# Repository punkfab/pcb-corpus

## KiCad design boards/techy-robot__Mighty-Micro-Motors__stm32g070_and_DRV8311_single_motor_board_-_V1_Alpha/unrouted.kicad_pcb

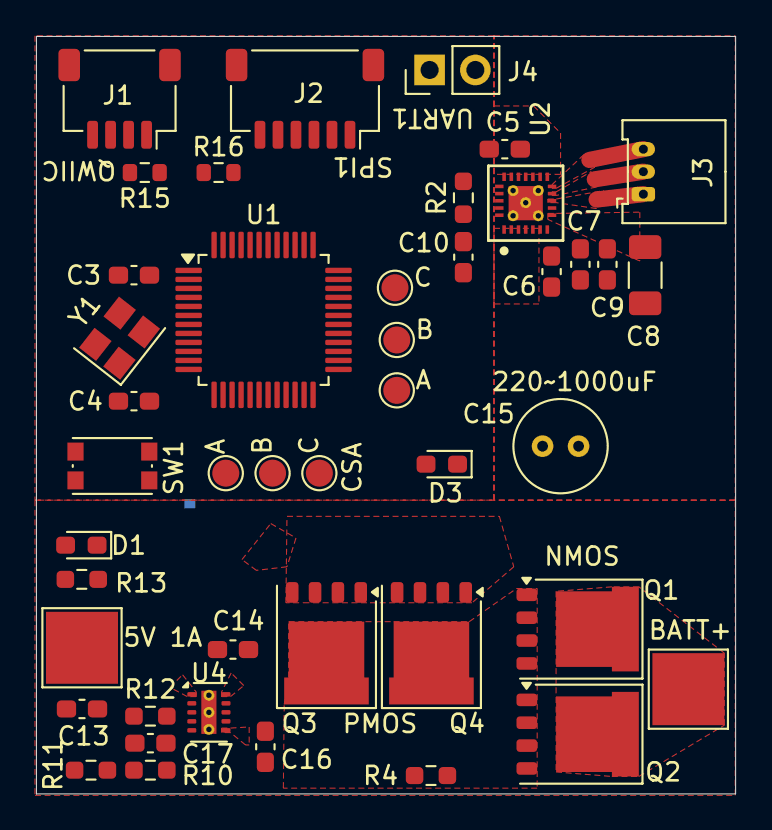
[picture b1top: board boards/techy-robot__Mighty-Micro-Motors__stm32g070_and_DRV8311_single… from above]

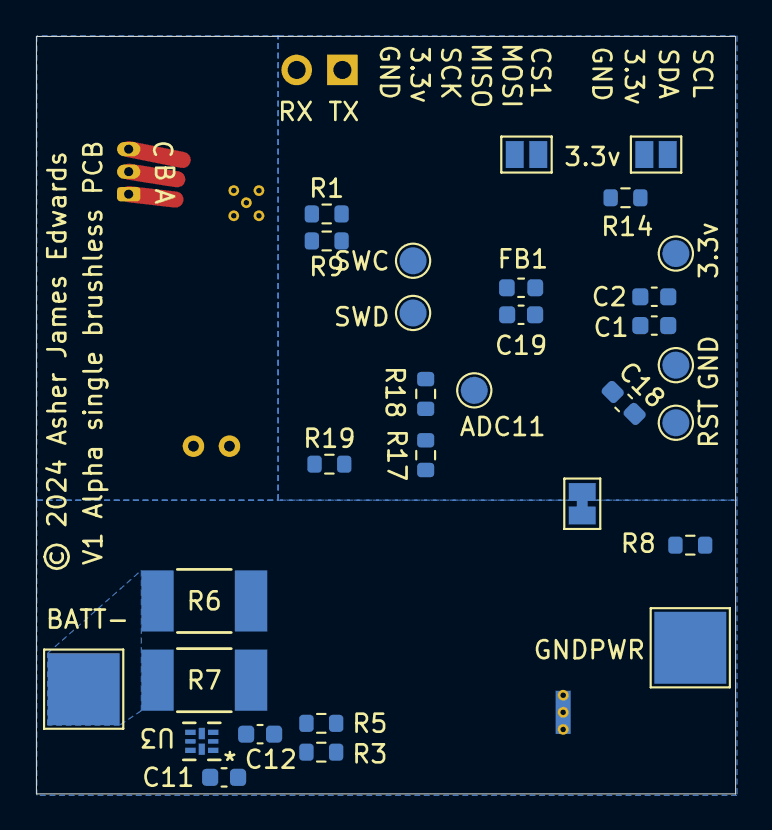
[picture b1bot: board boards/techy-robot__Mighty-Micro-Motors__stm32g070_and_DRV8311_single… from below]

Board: 4 copper layers, 38.8 x 42.1 mm, 74 parts (30 on the bottom side), 51 nets, no tracks yet.

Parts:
C1, C19: 0.1uF; C_0603_1608Metric
C2: 4.7uF; C_0603_1608Metric
C3, C4: 12pF; C_0603_1608Metric_Pad1.08x0.95mm_HandSolder
C5: 4.7uF; C_0603_1608Metric_Pad1.08x0.95mm_HandSolder
C6, C7, C9: 0.1uF, 16v; C_0603_1608Metric_Pad1.08x0.95mm_HandSolder
C8: 220uF, 16 v; C_1206_3216Metric_Pad1.33x1.80mm_HandSolder
C10, C18: 0.1uF; C_0603_1608Metric_Pad1.08x0.95mm_HandSolder
C11: 8nF; C_0603_1608Metric
C12: 1uF, 16v; C_0603_1608Metric
C13, C14, C16: 10uF, 16v; C_0603_1608Metric_Pad1.08x0.95mm_HandSolder
C15: 1000uF, 16v; C_Radial_D5.0mm_H5.0mm_P2.00mm
C17: 1uF; C_0603_1608Metric_Pad1.08x0.95mm_HandSolder
D1, D3: Osram LT Q99G.01 green led; LED_0603_1608Metric_Pad1.05x0.95mm_HandSolder
FB1: 120ohm imp @100mhz; L_0603_1608Metric
H1, H2, H3, H4: 4mm_Pad; TestPoint_Pad_4.0x4.0mm
J1: JST SH SM04B; JST_SH_SM04B-SRSS-TB_1x04-1MP_P1.00mm_Horizontal
J2: JST SH SM06B; JST_SH_SM06B-SRSS-TB_1x06-1MP_P1.00mm_Horizontal
J3: Molex_PicoBlade_53048-0310 Horizontal 3P; Molex_PicoBlade_53048-0310_1x03_P1.25mm_Horizontal
J4: Conn_01x02_Pin; PinHeader_1x02_P2.54mm_Vertical
JP1, JP2: VCC; SolderJumper-2_P1.3mm_Bridged_Pad1.0x1.5mm
L1: GND joiner; SolderJumper-2_P1.3mm_Bridged_Pad1.0x1.5mm
Q1: NMOS, sir404dp; PQFN-8-EP_6x5mm_P1.27mm_Generic
Q2: NMOS; PQFN-8-EP_6x5mm_P1.27mm_Generic
Q3: PMOS,Si7157DP; PQFN-8-EP_6x5mm_P1.27mm_Generic
Q4: PMOS; PQFN-8-EP_6x5mm_P1.27mm_Generic
R1, R17: 100k; R_0603_1608Metric
R2: 47k; R_0603_1608Metric_Pad0.98x0.95mm_HandSolder
R3: 20ohm; R_0603_1608Metric
R4, R13: 2k; R_0603_1608Metric_Pad0.98x0.95mm_HandSolder
R5: 300ohm; R_0603_1608Metric
R6: Same, 1000uOhm; RES_WSLF2512_VIS-M
R7: Vishay WSLF2512, 1%, 300uOhm; RES_WSLF2512_VIS-M
R8: 402 ohm; R_0603_1608Metric
R9, R18: 150k; R_0603_1608Metric
R10, R12: 1k; R_0603_1608Metric_Pad0.98x0.95mm_HandSolder
R11: 230ohm; R_0603_1608Metric_Pad0.98x0.95mm_HandSolder
R14, R15, R16: 10k; R_0603_1608Metric
R19: 80.6 ohm; R_0603_1608Metric
SW1: SW_Push; SW_Push_1P1T_NO_CK_KMR2
TP1, TP2, TP3, TP4, TP5, TP6: TestPoint; TestPoint_Pad_D1.5mm
TP7, TP8, TP9, TP10, TP11, TP12: TestPoint_Pad_D1.5mm
U1: STM32G070CBTr; LQFP-48_7x7mm_P0.5mm
U2: DRV8311HRRWR; DRV8311_0.3mmVias
U3: BQ298012RUGT; RUG8_TEX
U4: BQ25060; WSON-10-1EP_2x3mm_P0.5mm_EP0.84x2.4mm_ThermalVias_0.3mm
Y1: ABM8-16.000MHZ-10-1-U-T; Crystal_SMD_Abracon_ABM8G-4Pin_3.2x2.5mm

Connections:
/1A: TP7.1, U1.20 (PB1), U1.26 (PB14), U1.27 (PB15), U2.15 (INHA)
/1B: TP8.1, U1.28 (PA8), U1.29 (PA9/NC), U1.30 (PC6), U2.14 (INHB)
/1C: TP9.1, U1.31 (PC7), U1.32 (PA10/NC), U1.33 (PA11/PA9), U2.13 (INHC)
/1CSA-A: TP10.1, U1.11 (PA0), U1.12 (PA1), U1.13 (PA2), U2.5 (SOA)
/1CSA-B: TP11.1, U1.14 (PA3), U1.15 (PA4), U1.16 (PA5), U2.4 (SOB)
/1CSA-C: TP12.1, U1.17 (PA6), U1.18 (PA7), U1.19 (PB0), U2.3 (SOC)
/ADC10/VBATT: R17.1, R18.2, U1.21 (PB2)
/ADC11: TP6.1, U1.22 (PB10)
/CS1: J2.6, R16.2, U1.40 (PD2)
/LED: R19.1, U1.24 (PB12)
/MISO1: J2.4, U1.43 (PB4)
/MOSI1: J2.5, U1.44 (PB5)
/MOTORPWR: C6.2, C7.1, C8.1, C9.1, C14.1, C15.1, Q3.1 (S), Q3.2 (S), Q3.3 (S), Q4.1 (S), Q4.2 (S), Q4.3 (S), R1.2, R17.2, U2.7 (VIN_AVDD), U2.8 (VM), U4.10 (OUT)
/NRST: C18.1, SW1.2, TP1.1, U1.10 (NRST)
/PSU/BATT+: H1.1, Q1.5 (D), Q2.5 (D), R3.1, R5.1
/PSU/BATT-: C12.2, H2.1, R6.1, R7.1, U3.3 (VSS), U3.5 (CTR)
/PSU/IN: C13.1, H3.1, U4.1 (IN)
/PSU/LDO 4.9v: C17.2, R8.1, R10.1, R13.2, U4.4 (LDO)
/PSU/Pack+: C16.2, Q1.1 (S), Q1.2 (S), Q1.3 (S), Q2.1 (S), Q2.2 (S), Q2.3 (S), Q3.5 (D), Q4.5 (D), R4.1, U4.6 (BAT)
/PSU/~CHG: D1.1 (K), R13.1, U4.8 (~CHG)
/SCK1: J2.3, U1.42 (PB3)
/SCL1: J1.4, R15.2, U1.47 (PB8)
/SDA1: J1.3, R14.2, U1.48 (PB9)
/SWC: TP3.1, U1.36 (PA14)
/SWD: TP2.1, U1.35 (PA13)
/USART1_RX: J4.2, U1.46 (PB7)
/USART1_TX: J4.1, U1.45 (PB6)
GND: C1.2, C2.2, C3.2, C4.2, C5.1, C7.2, C10.1, C17.1, C18.2, C19.1, D3.1 (K), J1.1, J1.MP (MountPin), J2.1, J2.MP (MountPin), L1.1, R2.1, R9.1, R11.2, R12.1, R18.1, SW1.1, TP5.1, U1.7 (VSS), U2.16 (AGND), U4.7 (EN), Y1.2, Y1.4
GNDPWR: C8.2, C9.2, C11.2, C13.2, C14.2, C15.2, C16.1, H4.1, L1.2, R6.2, R7.2, U2.9 (PGND), U2.25 (PowerPAD), U3.4 (CS), U4.3 (VSS), U4.11 (VSS)
unnamed: D1.2 (A), R8.2
unnamed: D3.2 (A), R19.2
unnamed: J1.2, JP1.2 (B)
unnamed: J2.2, JP2.2 (B)
unnamed: J3.1, U2.10 (OUTA)
unnamed: J3.2, U2.11 (OUTB)
unnamed: J3.3, U2.12 (OUTC)
unnamed: Q1.4 (G), Q2.4 (G), U3.7 (DSG)
unnamed: Q3.4 (G), Q4.4 (G), U4.9 (BGATE)
unnamed: C3.1, U1.8 (PF0), Y1.3
unnamed: C4.1, U1.9 (PF1), Y1.1
unnamed: C19.2, FB1.1, U1.5 (VREF+)
unnamed: C6.1, U2.6 (CP)
unnamed: R2.2, U2.21 (GAIN)
unnamed: R1.1, R9.2, U2.24 (SLEEP_N)
unnamed: R3.2, U3.1 (BAT)
unnamed: C11.1, U3.8 (CHG)
unnamed: R4.2, U3.6 (PACK)
unnamed: C12.1, R5.2, U3.2 (VDD)
unnamed: R12.2, U4.2 (ISET)
unnamed: R10.2, R11.1, U4.5 (TS)
VDD: C1.1, C2.1, C5.2, C10.2, FB1.2, JP1.1 (A), JP2.1 (A), R14.1, R15.1, R16.1, TP4.1, U1.4 (VBAT), U1.6 (VDD), U2.2 (CSAREF), U2.17 (AVDD), U2.18 (INLA), U2.19 (INLB), U2.20 (INLC), U2.23 (MODE)

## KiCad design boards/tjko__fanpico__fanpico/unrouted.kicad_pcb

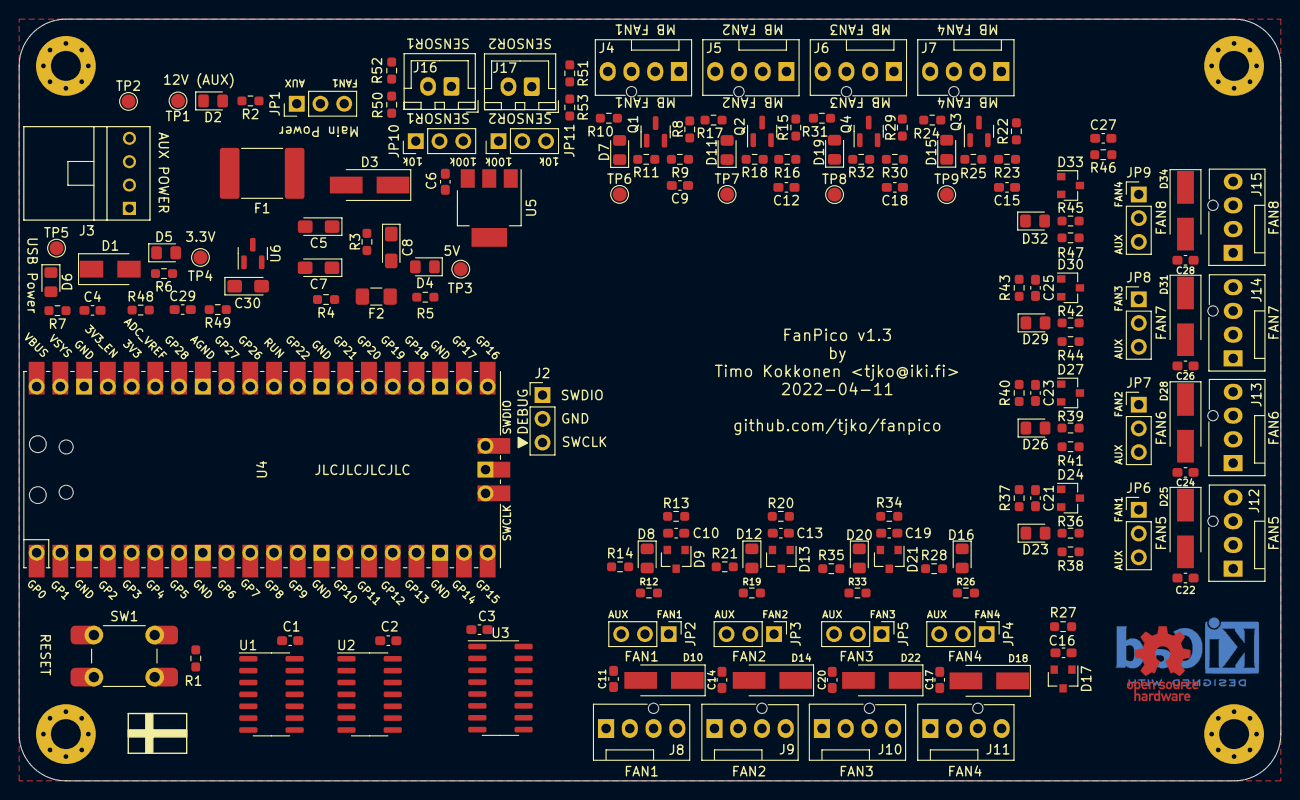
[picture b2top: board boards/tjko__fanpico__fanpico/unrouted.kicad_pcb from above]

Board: 2 copper layers, 135.0 x 81.5 mm, 170 parts (0 on the bottom side), 116 nets, no tracks yet.

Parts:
C1, C2, C3, C4, C6, C11, C14, C17, C20, C22, C24, C26, C28, C29: 0.1uF; C_0603_1608Metric_Pad1.08x0.95mm_HandSolder
C5: 10uF 20V; CP_EIA-3216-18_Kemet-A_Pad1.58x1.35mm_HandSolder
C7, C8, C30: 10uF 16V; CP_EIA-3216-18_Kemet-A_Pad1.58x1.35mm_HandSolder
C9, C12, C15, C18: DNF; C_0603_1608Metric_Pad1.08x0.95mm_HandSolder
C10, C13, C16, C19, C21, C23, C25, C27: 1nF; C_0603_1608Metric_Pad1.08x0.95mm_HandSolder
D1: SM5819PL 1A 40V; D_SMA
D2, D4, D5, D6, D7, D8, D11, D12, D15, D16, D19, D20, D23, D26, D29, D32: LED 0805 (green); LED_0805_2012Metric_Pad1.15x1.40mm_HandSolder
D3, D10, D14, D18, D22, D25, D28, D31, D34: ES1D 1A 200V; D_SMA_Handsoldering
D9, D13, D17, D21, D24, D27, D30, D33: BAT54C; D_SOT-23_ANK
F1: Polyfuse 3A; Fuse_2920_7451Metric_Pad2.10x5.45mm_HandSolder
F2: Polyfuse 0.5A; Fuse_1206_3216Metric_Pad1.42x1.75mm_HandSolder
H1, H2, H3, H4: MountingHole_Pad; MountingHole_3.2mm_M3_Pad_Via
J2: Pico Debug; PinHeader_1x03_P2.54mm_Vertical
J3: Floppy Power Connector; TE 171826-4 Floppy 4-pin
J4: MB Fan1 Input; FanPinHeader_1x04_P2.54mm_Vertical
J5: MB Fan2 Input; FanPinHeader_1x04_P2.54mm_Vertical
J6: MB Fan3 Input; FanPinHeader_1x04_P2.54mm_Vertical
J7: MB Fan4 Input; FanPinHeader_1x04_P2.54mm_Vertical
J8: Fan1 Output; FanPinHeader_1x04_P2.54mm_Vertical
J9: Fan2 Output; FanPinHeader_1x04_P2.54mm_Vertical
J10: Fan3 Output; FanPinHeader_1x04_P2.54mm_Vertical
J11: Fan4 Output; FanPinHeader_1x04_P2.54mm_Vertical
J12: Fan5 Output; FanPinHeader_1x04_P2.54mm_Vertical
J13: Fan6 Output; FanPinHeader_1x04_P2.54mm_Vertical
J14: Fan7 Output; FanPinHeader_1x04_P2.54mm_Vertical
J15: Fan8 Output; FanPinHeader_1x04_P2.54mm_Vertical
J16: Sensor1; JST_XH_B2B-XH-A_1x02_P2.50mm_Vertical
J17: Sensor2; JST_XH_B2B-XH-A_1x02_P2.50mm_Vertical
JP1: Power Selector; PinHeader_1x03_P2.54mm_Vertical
JP2, JP3, JP4, JP5, JP6, JP7, JP8, JP9: Fan Power; PinHeader_1x03_P2.54mm_Vertical
JP10, JP11: NTC Value; PinHeader_1x03_P2.54mm_Vertical
Q1, Q2, Q3, Q4: 2N7002K; SOT-23
R1, R4, R8, R11, R15, R18, R22, R25, R29, R32: 1k; R_0603_1608Metric_Pad0.98x0.95mm_HandSolder
R2, R10, R12, R17, R19, R24, R26, R31, R33, R36, R39, R42, R45: 49.9k; R_0603_1608Metric_Pad0.98x0.95mm_HandSolder
R3, R48: 330; R_0603_1608Metric_Pad0.98x0.95mm_HandSolder
R5, R7, R13, R20, R27, R34, R37, R40, R43, R46, R50, R51: 10k; R_0603_1608Metric_Pad0.98x0.95mm_HandSolder
R6: 4.99k; R_0603_1608Metric_Pad0.98x0.95mm_HandSolder
R9, R16, R23, R30: 30k; R_0603_1608Metric_Pad0.98x0.95mm_HandSolder
R14, R21, R28, R35, R38, R41, R44, R47: 680; R_0603_1608Metric_Pad0.98x0.95mm_HandSolder
R49: 0; R_0603_1608Metric_Pad0.98x0.95mm_HandSolder
R52, R53: 100k; R_0603_1608Metric_Pad0.98x0.95mm_HandSolder
SW1: SW_Push; SW_PUSH_6mm_SMD_2
TP1, TP2, TP3, TP4, TP5, TP6, TP7, TP8, TP9: TestPoint; TestPoint_Pad_D1.5mm
U1, U2: SN74AHCT125QDRQ1; SOIC-14_3.9x8.7mm_P1.27mm
U3: CD74HC4050NSR; SOIC-16_3.9x9.9mm_P1.27mm
U4: Pico; RPi_Pico_SMD_TH
U5: SPX1117-ADJ; SOT-223
U6: LM4040DBZ-3; SOT-23

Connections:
3V3: C3.1, R6.1, R9.2, R13.2, R16.2, R20.2, R23.2, R27.2, R30.2, R34.2, R37.2, R40.2, R43.2, R46.2, R48.1, TP4.1, U3.1 (VCC), U4.36 (3V3)
+5V: C1.1, C2.1, D1.2 (A), F2.2, R5.1, TP3.1, U1.14 (VCC), U2.14 (VCC)
/Fan Channels/Fan1/PWM_IN: J4.4, R8.2
/Fan Channels/Fan1/PWM_OUT: J8.4, R14.2
/Fan Channels/Fan1/PWR_OUT: C11.1, D10.1 (K), J8.2, JP2.2 (C), R12.1
/Fan Channels/Fan1/TACHO_IN: D9.1 (K), J8.3
/Fan Channels/Fan1/TACHO_OUT: J4.3, Q1.3 (D)
/Fan Channels/Fan2/PWM_IN: J5.4, R15.2
/Fan Channels/Fan2/PWM_OUT: J9.4, R21.2
/Fan Channels/Fan2/PWR_OUT: C14.1, D14.1 (K), J9.2, JP3.2 (C), R19.1
/Fan Channels/Fan2/TACHO_IN: D13.1 (K), J9.3
/Fan Channels/Fan2/TACHO_OUT: J5.3, Q2.3 (D)
/Fan Channels/Fan3/PWM_IN: J6.4, R29.2
/Fan Channels/Fan3/PWM_OUT: J10.4, R35.2
/Fan Channels/Fan3/PWR_OUT: C20.1, D22.1 (K), J10.2, JP5.2 (C), R33.1
/Fan Channels/Fan3/TACHO_IN: D21.1 (K), J10.3
/Fan Channels/Fan3/TACHO_OUT: J6.3, Q4.3 (D)
/Fan Channels/Fan4/PWM_IN: J7.4, R22.2
/Fan Channels/Fan4/PWM_OUT: J11.4, R28.2
/Fan Channels/Fan4/PWR_OUT: C17.1, D18.1 (K), J11.2, JP4.2 (C), R26.1
/Fan Channels/Fan4/TACHO_IN: D17.1 (K), J11.3
/Fan Channels/Fan4/TACHO_OUT: J7.3, Q3.3 (D)
/Fan Channels/Fan5/PWM_OUT: J12.4, R38.2
/Fan Channels/Fan5/PWR_OUT: C22.1, D25.1 (K), J12.2, JP6.2 (C), R36.1
/Fan Channels/Fan5/TACHO_IN: D24.1 (K), J12.3
/Fan Channels/Fan6/PWM_OUT: J13.4, R41.2
/Fan Channels/Fan6/PWR_OUT: C24.1, D28.1 (K), J13.2, JP7.2 (C), R39.1
/Fan Channels/Fan6/TACHO_IN: D27.1 (K), J13.3
/Fan Channels/Fan7/PWM_OUT: J14.4, R44.2
/Fan Channels/Fan7/PWR_OUT: C26.1, D31.1 (K), J14.2, JP8.2 (C), R42.1
/Fan Channels/Fan7/TACHO_IN: D30.1 (K), J14.3
/Fan Channels/Fan8/PWM_OUT: J15.4, R47.2
/Fan Channels/Fan8/PWR_OUT: C28.1, D34.1 (K), J15.2, JP9.2 (C), R45.1
/Fan Channels/Fan8/TACHO_IN: D33.1 (K), J15.3
/PWM0B: U3.6 (3Y), U4.22 (GPIO17)
/PWM1B: U3.10 (4Y), U4.25 (GPIO19)
/PWM2A: U1.2 (1A), U4.6 (GPIO4)
/PWM2B: U1.5 (2A), U4.7 (GPIO5)
/PWM3A: U1.9 (3A), U4.9 (GPIO6)
/PWM3B: U1.12 (4A), U4.10 (GPIO7)
/PWM4A: U2.2 (1A), U4.11 (GPIO8)
/PWM4B: U2.5 (2A), U4.12 (GPIO9)
/PWM5A: U2.9 (3A), U4.14 (GPIO10)
/PWM5B: U2.12 (4A), U4.15 (GPIO11)
/PWM6B: U3.2 (1Y), U4.17 (GPIO13)
/PWM7B: U3.4 (2Y), U4.20 (GPIO15)
/SWCLK: J2.3, U4.41 (SWCLK)
/SWDIO: J2.1, U4.43 (SWDIO)
ADC_REF: C29.1, C30.1, JP10.2 (C), JP11.2 (C), R48.2, U4.35 (ADC_VREF), U6.1 (K)
AGND: C29.2, C30.2, J16.1, J17.1, R49.1, U4.33 (AGND), U6.2 (A)
AUX5V: J3.1, TP2.1
AUX12V: F1.2, JP1.1 (A), JP2.3 (B), JP3.3 (B), JP4.3 (B), JP5.3 (B), JP6.3 (B), JP7.3 (B), JP8.3 (B), JP9.3 (B), R2.1, TP1.1
FAN1_PWM_GEN: R14.1, U1.3 (1Y)
FAN1_PWR: J4.2, JP1.3 (B), JP2.1 (A), JP6.1 (A), R10.1, TP6.1
FAN1_TACHO_READ: C10.1, D9.2 (A), R13.1, U4.4 (GPIO2)
FAN2_PWM_GEN: R21.1, U1.6 (2Y)
FAN2_PWR: J5.2, JP3.1 (A), JP7.1 (A), R17.1, TP7.1
FAN2_TACHO_READ: C13.1, D13.2 (A), R20.1, U4.5 (GPIO3)
FAN3_PWM_GEN: R35.1, U1.8 (3Y)
FAN3_PWR: J6.2, JP5.1 (A), JP8.1 (A), R31.1, TP8.1
FAN3_TACHO_READ: C19.1, D21.2 (A), R34.1, U4.26 (GPIO20)
FAN4_PWM_GEN: R28.1, U1.11 (4Y)
FAN4_PWR: J7.2, JP4.1 (A), JP9.1 (A), R24.1, TP9.1
FAN4_TACHO_READ: C16.1, D17.2 (A), R27.1, U4.27 (GPIO21)
FAN5_PWM_GEN: R38.1, U2.3 (1Y)
FAN5_TACHO_READ: C21.1, D24.2 (A), R37.1, U4.29 (GPIO22)
FAN6_PWM_GEN: R41.1, U2.6 (2Y)
FAN6_TACHO_READ: C23.1, D27.2 (A), R40.1, U4.31 (GPIO26_ADC0)
FAN7_PWM_GEN: R44.1, U2.8 (3Y)
FAN7_TACHO_READ: C25.1, D30.2 (A), R43.1, U4.2 (GPIO1)
FAN8_PWM_GEN: R47.1, U2.11 (4Y)
FAN8_TACHO_READ: C27.1, D33.2 (A), R46.1, U4.1 (GPIO0)
GND: C1.2, C2.2, C3.2, C4.2, C5.2, C6.2, C7.2, C8.2, C9.2, C10.2, C11.2, C12.2, C13.2, C14.2, C15.2, C16.2, C17.2, C18.2, C19.2, C20.2, C21.2, C22.2, C23.2, C24.2, C25.2, C26.2, C27.2, C28.2, D2.1 (K), D4.1 (K), D5.1 (K), D6.1 (K), D7.1 (K), D8.1 (K), D10.2 (A), D11.1 (K), D12.1 (K), D14.2 (A), D15.1 (K), D16.1 (K), D18.2 (A), D19.1 (K), D20.1 (K), D22.2 (A), D23.1 (K), D25.2 (A), D26.1 (K), D28.2 (A), D29.1 (K), D31.2 (A), D32.1 (K), D34.2 (A), H1.1, H2.1, H3.1, H4.1, J2.2, J3.2, J3.3, J4.1, J5.1, J6.1, J7.1, J8.1, J9.1, J10.1, J11.1, J12.1, J13.1, J14.1, J15.1, Q1.2 (S), Q2.2 (S), Q3.2 (S), Q4.2 (S), R4.2, R49.2, SW1.2, U1.1 (~1OE), U1.4 (~2OE), U1.7 (GND), U1.10 (~3OE), U1.13 (~4OE), U2.1 (~1OE), U2.4 (~2OE), U2.7 (GND), U2.10 (~3OE), U2.13 (~4OE), U3.8 (GND), U3.11 (5A), U3.14 (6A), U4.3 (GND), U4.8 (GND), U4.13 (GND), U4.18 (GND), U4.23 (GND), U4.28 (GND), U4.38 (GND), U4.42 (GND)
MBFAN1_PWM_READ: C9.1, R8.1, R9.1, U3.3 (1A)
MBFAN1_TACHO_GEN: R11.2, U4.16 (GPIO12)
MBFAN2_PWM_READ: C12.1, R15.1, R16.1, U3.5 (2A)
MBFAN2_TACHO_GEN: R18.2, U4.19 (GPIO14)
MBFAN3_PWM_READ: C18.1, R29.1, R30.1, U3.7 (3A)
MBFAN3_TACHO_GEN: R32.2, U4.21 (GPIO16)
MBFAN4_PWM_READ: C15.1, R22.1, R23.1, U3.9 (4A)
MBFAN4_TACHO_GEN: R25.2, U4.24 (GPIO18)
unnamed: C4.1, D1.1 (K), U4.39 (VSYS)
unnamed: C5.1, C6.1, D3.1 (K), U5.3 (VI)
unnamed: C7.1, R3.2, R4.1, U5.1 (ADJ)
unnamed: C8.1, F2.1, R3.1, U5.2 (VO)
unnamed: D2.2 (A), R2.2
unnamed: D3.2 (A), JP1.2 (C)
unnamed: D4.2 (A), R5.2
unnamed: D5.2 (A), R6.2
unnamed: D6.2 (A), R7.2
unnamed: D7.2 (A), R10.2
unnamed: D8.2 (A), R12.2
unnamed: D11.2 (A), R17.2
unnamed: D12.2 (A), R19.2
unnamed: D15.2 (A), R24.2
unnamed: D16.2 (A), R26.2
unnamed: D19.2 (A), R31.2
unnamed: D20.2 (A), R33.2
unnamed: D23.2 (A), R36.2
unnamed: D26.2 (A), R39.2
unnamed: D29.2 (A), R42.2
unnamed: D32.2 (A), R45.2
unnamed: F1.1, J3.4
unnamed: JP10.1 (A), R50.2
unnamed: JP10.3 (B), R52.2
unnamed: JP11.1 (A), R51.2
unnamed: JP11.3 (B), R53.2
unnamed: Q1.1 (G), R11.1
unnamed: Q2.1 (G), R18.1
unnamed: Q3.1 (G), R25.1
unnamed: Q4.1 (G), R32.1
unnamed: R1.2, SW1.1
RESET: R1.1, U4.30 (RUN)
TEMP1_READ: J16.2, R50.1, R52.1, U4.32 (GPIO27_ADC1)
TEMP2_READ: J17.2, R51.1, R53.1, U4.34 (GPIO28_ADC2)
VBUS: R7.1, TP5.1, U4.40 (VBUS)

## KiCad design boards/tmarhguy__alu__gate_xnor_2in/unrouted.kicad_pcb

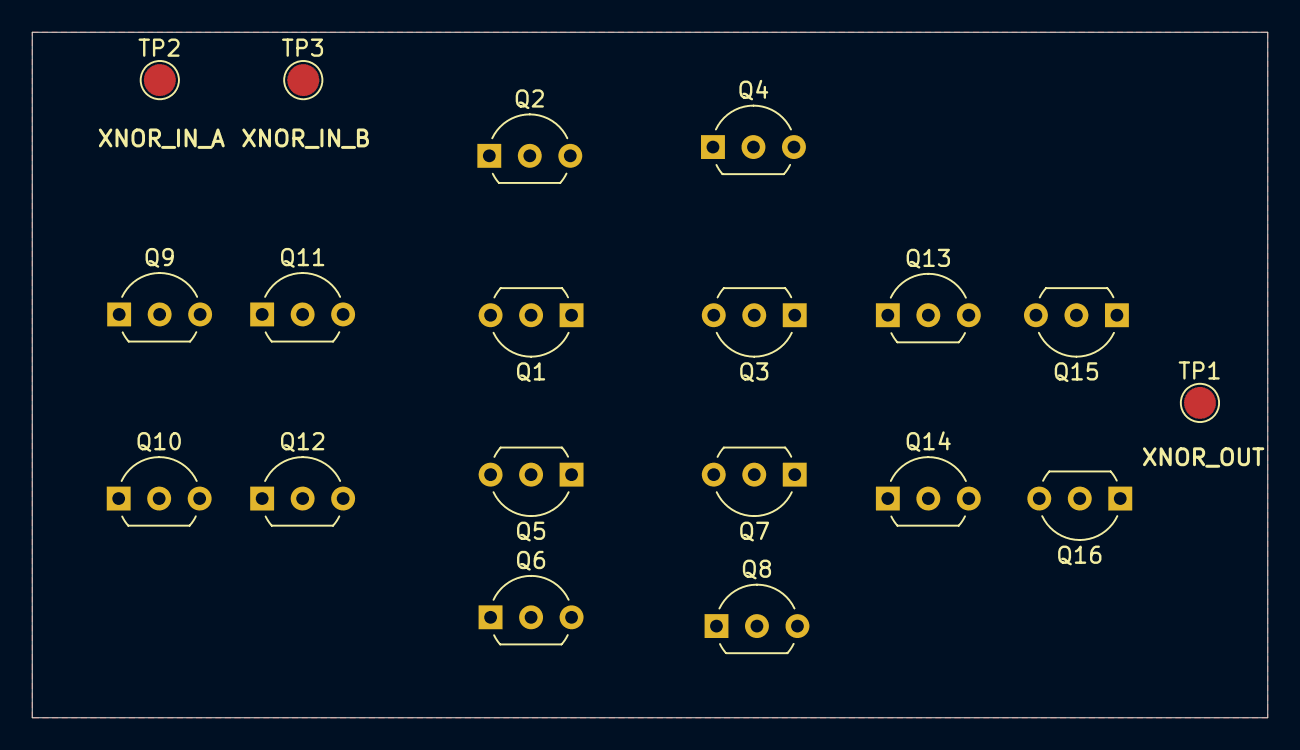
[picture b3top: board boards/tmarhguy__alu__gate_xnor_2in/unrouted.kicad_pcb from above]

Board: 2 copper layers, 77.5 x 43.0 mm, 19 parts (0 on the bottom side), 13 nets, no tracks yet.

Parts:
Q1, Q2, Q3, Q4, Q9, Q11, Q13, Q15: PMOS; TO-92L_Inline_Wide
Q5, Q6, Q7, Q8, Q10, Q12, Q14, Q16: NMOS; TO-92L_Inline_Wide
TP1: XNOR_OUT; TestPoint_Pad_D2.0mm
TP2: XNOR_IN_A; TestPoint_Pad_D2.0mm
TP3: XNOR_IN_B; TestPoint_Pad_D2.0mm

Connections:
/XNOR_IN_A: Q2.2 (G), Q5.2 (G), Q9.2 (G), Q10.2 (G), TP2.1
/XNOR_IN_B: Q1.2 (G), Q8.2 (G), Q11.2 (G), Q12.2 (G), TP3.1
/XNOR_OUT: Q15.1 (D), Q16.1 (D), TP1.1
GND: Q6.3 (S), Q8.3 (S), Q10.3 (S), Q12.3 (S), Q14.3 (S), Q16.3 (S)
unnamed: Q1.1 (D), Q3.1 (D), Q5.1 (D), Q7.1 (D), Q13.2 (G), Q14.2 (G)
unnamed: Q1.3 (S), Q2.1 (D)
unnamed: Q3.3 (S), Q4.1 (D)
unnamed: Q5.3 (S), Q6.1 (D)
unnamed: Q7.3 (S), Q8.1 (D)
unnamed: Q4.2 (G), Q7.2 (G), Q9.1 (D), Q10.1 (D)
unnamed: Q3.2 (G), Q6.2 (G), Q11.1 (D), Q12.1 (D)
unnamed: Q13.1 (D), Q14.1 (D), Q15.2 (G), Q16.2 (G)
VCC: Q2.3 (S), Q4.3 (S), Q9.3 (S), Q11.3 (S), Q13.3 (S), Q15.3 (S)

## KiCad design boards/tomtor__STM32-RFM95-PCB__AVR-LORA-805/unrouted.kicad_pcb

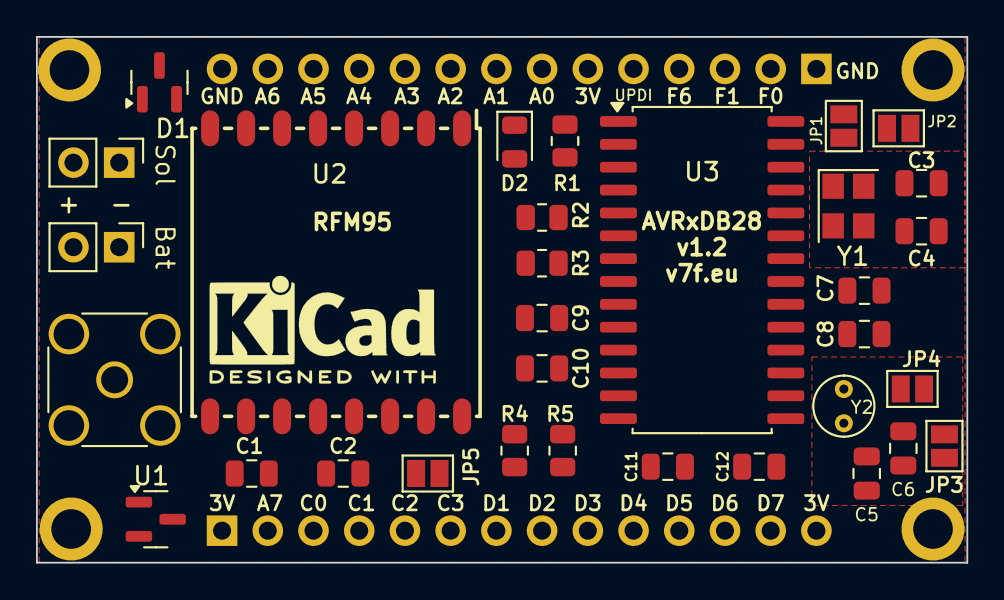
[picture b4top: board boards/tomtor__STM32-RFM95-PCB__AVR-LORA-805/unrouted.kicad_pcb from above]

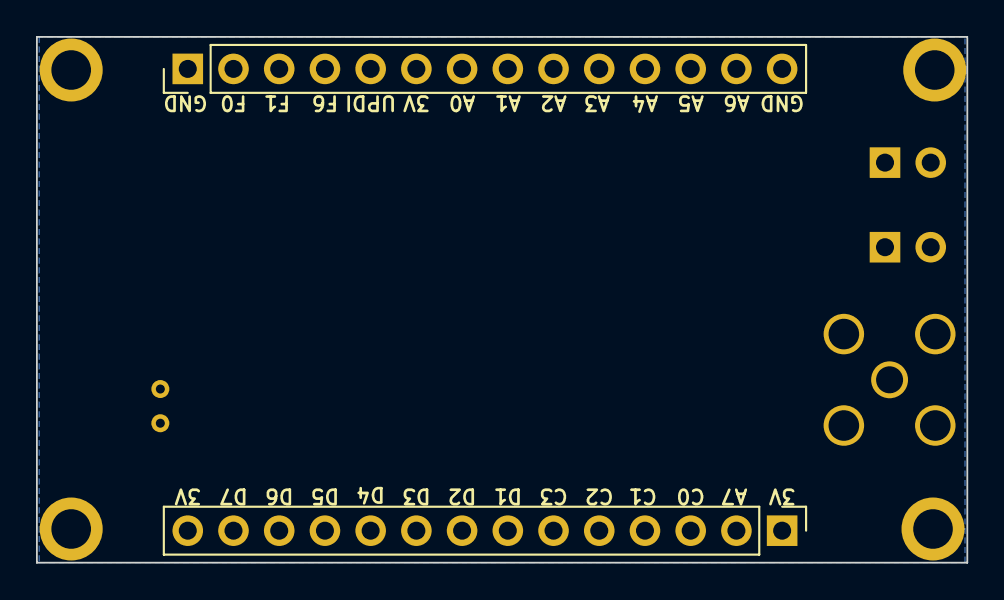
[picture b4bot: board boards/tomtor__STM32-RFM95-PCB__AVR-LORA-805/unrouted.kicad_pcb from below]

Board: 2 copper layers, 51.7 x 29.2 mm, 34 parts (2 on the bottom side), 33 nets, no tracks yet.

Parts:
C1, C2, C8, C10, C12: 1uF; C_0805_2012Metric
C3, C4: 20pF; C_0805_2012Metric
C5, C6: 10pF; C_0805_2012Metric
C7, C9, C11: 100nF; C_0805_2012Metric
D1: BAT54S; SOT-23
D2: LED; LED_0805_2012Metric
J1: Batt; PinHeader_1x02_P2.54mm_Vertical
J2: Solar; PinHeader_1x02_P2.54mm_Vertical
J3: SMA; SMA_Amphenol_132134_Vertical
J4, J5: CONN_01X14; PinHeader_1x14_P2.54mm_Vertical
JP1, JP2, JP3, JP4: SolderJumper_2_Open; SolderJumper-2_P1.3mm_Open_Pad1.0x1.5mm
JP5: Close when no MCP1700; SolderJumper-2_P1.3mm_Open_Pad1.0x1.5mm
R1: 100R; R_0805_2012Metric
R2, R3: 4K7; R_0805_2012Metric
R4, R5: 1M; R_0805_2012Metric
U1: MCP1700-3302E_SOT23; SOT-23
U2: RFM95HW; RFM95
U3: AVR128DB28; SOIC-28W_7.5x17.9mm_P1.27mm
Y1: 24MHz; Crystal_SMD_Abracon_ABM8G-4Pin_3.2x2.5mm
Y2: 32768Hz; Crystal_Round_D3.0mm_Vertical

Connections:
/3V3: C2.1, C7.2, C8.2, C9.2, C10.2, C11.2, C12.2, J4.1, J4.14, J5.6, JP5.2 (B), R2.1, R3.1, U1.2 (VO), U2.13 (3.3V), U3.6 (VDDIO2), U3.14 (AVDD), U3.20 (VDD)
/A0: C4.1, JP2.1 (A), U3.22 (PA0/XTALHF1), Y1.3
/A1: C3.1, JP1.1 (A), U3.23 (PA1/XTALHF2), Y1.1
/A2: J5.9, R3.2, U3.24 (PA2)
/A3: J5.10, R2.2, U3.25 (PA3)
/A4: J5.11, U2.3 (MOSI), U3.26 (PA4)
/A5: J5.12, U2.2 (MISO), U3.27 (PA5)
/A6: J5.13, U2.4 (SCK), U3.28 (PA6)
/A7: J4.2, R1.1, U3.1 (PA7)
/C0: J4.3, U3.2 (PC0)
/C1: J4.4, U3.3 (PC1)
/C2: J4.5, U3.4 (PC2)
/C3: J4.6, U3.5 (PC3)
/CA0: J5.7, JP2.2 (B)
/CA1: J5.8, JP1.2 (B)
/CF0: J5.2, JP3.2 (B)
/CF1: J5.3, JP4.2 (B)
/D1: J4.7, R4.2, R5.1, U3.7 (PD1)
/D2: J4.8, U2.14 (DIO0), U3.8 (PD2)
/D3: J4.9, U2.15 (DIO1), U3.9 (PD3)
/D4: J4.10, U2.16 (DIO2), U3.10 (PD4)
/D5: J4.11, U2.6 (RESET), U3.11 (PD5)
/D6: J4.12, U2.5 (NSS), U3.12 (PD6)
/D7: J4.13, U3.13 (PD7)
/F0: C5.1, JP3.1 (A), U3.16 (PF0/XTAL32K1), Y2.1
/F1: C6.1, JP4.1 (A), U3.17 (PF1/XTAL32K2), Y2.2
/F6: J5.4, U3.18 (PF6)
/UPDI: J5.5, U3.19 (UPDI)
GND: C1.2, C2.2, C3.2, C4.2, C5.2, C6.2, C7.1, C8.1, C9.1, C10.1, C11.1, C12.1, D2.1 (K), J1.1, J2.1, J3.2 (Ext), J5.1, J5.14, R5.2, U1.1 (GND), U2.1 (GND), U2.8 (GND), U2.10 (GND), U3.15 (GND), U3.21 (GND), Y1.2, Y1.4
unnamed: D1.1 (A), J2.2
unnamed: D2.2 (A), R1.2
unnamed: J3.1 (In), U2.9 (ANA)
VCC: C1.1, D1.3 (COM), J1.2, JP5.1 (A), R4.1, U1.3 (VI)

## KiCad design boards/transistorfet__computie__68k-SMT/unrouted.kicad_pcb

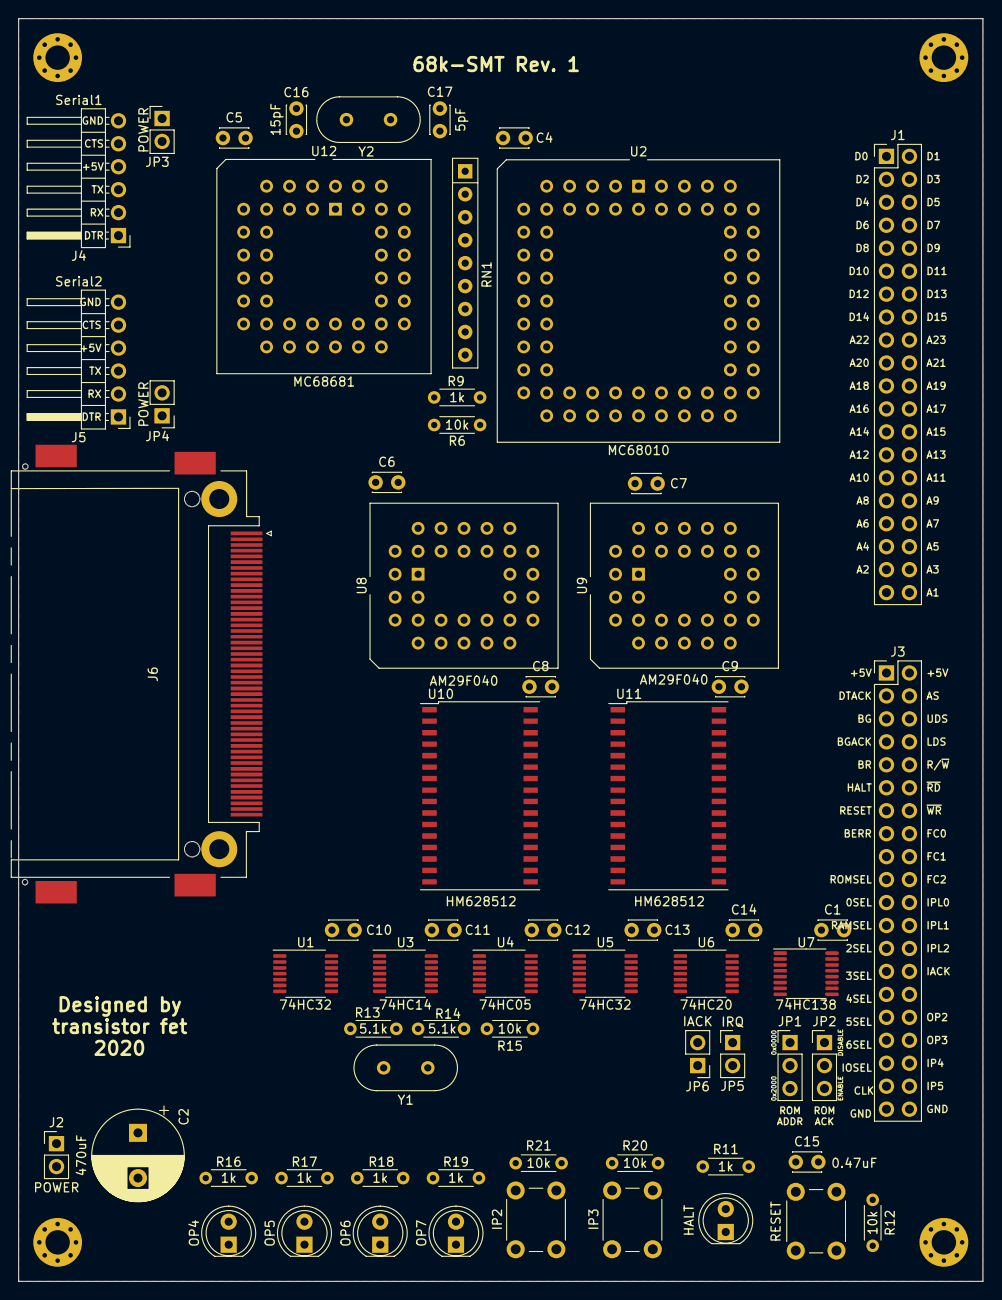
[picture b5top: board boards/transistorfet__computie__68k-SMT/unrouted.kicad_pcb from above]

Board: 2 copper layers, 106.7 x 139.7 mm, 68 parts (0 on the bottom side), 115 nets, no tracks yet.

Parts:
C1, C4, C5, C6, C7, C8, C9, C10, C11, C12, C13, C14: 0.1uF; C_Disc_D3.0mm_W2.0mm_P2.50mm
C2: 470uF; CP_Radial_D10.0mm_P5.00mm
C15: 0.47uF; C_Disc_D3.0mm_W2.0mm_P2.50mm
C16: 15pF; C_Disc_D3.0mm_W2.0mm_P2.50mm
C17: 5pF; C_Disc_D3.0mm_W2.0mm_P2.50mm
D1: HALT; LED_D5.0mm
D2: OP4; LED_D5.0mm
D3: OP5; LED_D5.0mm
D4: OP6; LED_D5.0mm
D5: OP7; LED_D5.0mm
H1, H2, H3, H4: .; MountingHole_2.7mm_Pad_Via
J1: ADBUS; PinHeader_2x20_P2.54mm_Vertical
J2: POWER; PinHeader_1x02_P2.54mm_Vertical
J3: SIGBUS; PinHeader_2x20_P2.54mm_Vertical
J4: Serial1; PinHeader_1x06_P2.54mm_Horizontal
J5: Serial2; PinHeader_1x06_P2.54mm_Horizontal
J6: CompactFlash; CF-Card_3M_N7E50-Q516RB-40
JP1: ROMJMP; PinHeader_1x03_P2.54mm_Vertical
JP2: ROMACK; PinHeader_1x03_P2.54mm_Vertical
JP3, JP4: POWER; PinHeader_1x02_P2.54mm_Vertical
JP5: IRQ; PinHeader_1x02_P2.54mm_Vertical
JP6: IACK; PinHeader_1x02_P2.54mm_Vertical
R6, R12, R15, R20, R21: 10k; R_Axial_DIN0204_L3.6mm_D1.6mm_P5.08mm_Horizontal
R9, R11, R16, R17, R18, R19: 1k; R_Axial_DIN0204_L3.6mm_D1.6mm_P5.08mm_Horizontal
R13, R14: 5.1k; R_Axial_DIN0204_L3.6mm_D1.6mm_P5.08mm_Horizontal
RN1: 10k; R_Array_SIP9
SW1: RESET; SW_PUSH_6mm
SW2: IP2; SW_PUSH_6mm
SW3: IP3; SW_PUSH_6mm
U1, U5: 74HC32; TSSOP-14_4.4x5mm_P0.65mm
U2: MC68010; PLCC-68_THT-Socket
U3: 74HC14; TSSOP-14_4.4x5mm_P0.65mm
U4: 74HC05; TSSOP-14_4.4x5mm_P0.65mm
U6: 74HC20; TSSOP-14_4.4x5mm_P0.65mm
U7: 74HC138; TSSOP-16_4.4x5mm_P0.65mm
U8, U9: AM29F040; PLCC-32_THT-Socket
U10, U11: HM628512; TSOP-II-32_21.0x10.2mm_P1.27mm
U12: MC68681; PLCC-44_THT-Socket
Y1, Y2: Crystal; Crystal_HC49-4H_Vertical

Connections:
0SEL: J3.21, JP1.1, JP2.1, U7.15
2SEL: J3.25, JP1.3, U7.13
3SEL: J3.27, U7.12
4SEL: J3.29, U7.11
5SEL: J3.31, U7.10
6SEL: J3.33, U1.9, U1.12, U7.9
+5V: C1.1, C2.1, C4.1, C5.1, C6.1, C7.1, C8.1, C9.1, C10.1, C11.1, C12.1, C13.1, C14.1, J2.1, J3.1, J3.2, J6.13, J6.36, J6.38, J6.44, JP2.3, JP3.1, JP4.1, R6.1, R9.1, R12.1, R15.1, R16.2, R17.2, R18.2, R19.2, RN1.1, SW2.2, SW3.2, U1.14, U2.14, U2.52, U3.14, U4.14, U5.14, U6.13, U6.14, U7.6, U7.16, U8.32, U9.32, U10.32, U11.32, U12.44
A1: J1.40, J6.20, U2.32, U8.12, U9.12, U10.12, U11.12, U12.2
A2: J1.37, J6.19, U2.33, U8.11, U9.11, U10.11, U11.11, U12.4
A3: J1.38, J6.18, U2.34, U8.10, U9.10, U10.10, U11.10, U12.6
A4: J1.35, J6.7, U2.35, U8.9, U9.9, U10.9, U11.9, U12.7
A5: J1.36, J6.32, U2.36, U8.8, U9.8, U10.8, U11.8
A6: J1.33, U2.37, U8.7, U9.7, U10.7, U11.7
A7: J1.34, U2.38, U8.6, U9.6, U10.6, U11.6
A8: J1.31, U2.39, U8.5, U9.5, U10.5, U11.5
A9: J1.32, U2.40, U8.27, U9.27, U10.27, U11.27
A10: J1.29, U2.41, U8.26, U9.26, U10.26, U11.26
A11: J1.30, U2.42, U8.23, U9.23, U10.23, U11.23
A12: J1.27, U2.43, U8.25, U9.25, U10.25, U11.25
A13: J1.28, U2.44, U8.4, U9.4, U10.4, U11.4
A14: J1.25, U2.45, U8.28, U9.28, U10.28, U11.28
A15: J1.26, U2.46, U8.29, U9.29, U10.3, U11.3
A16: J1.23, U2.47, U8.3, U9.3, U10.31, U11.31
A17: J1.24, U2.48, U8.2, U9.2, U10.2, U11.2
A18: J1.21, U2.49, U8.30, U9.30, U10.30, U11.30
A19: J1.22, U2.50, U8.1, U9.1, U10.1, U11.1
A20: J1.19, U2.51, U7.1
A21: J1.20, U2.53, U7.2
A22: J1.17, U2.54, U7.3
A23: J1.18, U2.55, U3.9, U7.5
AS: J3.4, U2.6, U3.11, U7.4
BERR: J3.15, RN1.6, U2.24
BG: J3.5, U2.11
BGACK: J3.7, RN1.4, U2.12
BR: J3.9, RN1.3, U2.13
CLK: J3.37, R14.1, U2.15, U3.6, Y1.2
D0: J1.1, J6.21, U2.5, U8.13, U10.13, U12.28
D1: J1.2, J6.22, U2.4, U8.14, U10.14, U12.18
D2: J1.3, J6.23, U2.3, U8.15, U10.15, U12.27
D3: J1.4, J6.2, U2.2, U8.17, U10.17, U12.19
D4: J1.5, J6.3, U2.1, U8.18, U10.18, U12.26
D5: J1.6, J6.4, U2.68, U8.19, U10.19, U12.20
D6: J1.7, J6.5, U2.67, U8.20, U10.20, U12.25
D7: J1.8, J6.6, U2.66, U8.21, U10.21, U12.21
D8: J1.9, J6.47, U2.65, U9.13, U11.13
D9: J1.10, J6.48, U2.64, U9.14, U11.14
D10: J1.11, J6.49, U2.63, U9.15, U11.15
D11: J1.12, J6.27, U2.62, U9.17, U11.17
D12: J1.13, J6.28, U2.61, U9.18, U11.18
D13: J1.14, J6.29, U2.60, U9.19, U11.19
D14: J1.15, J6.30, U2.59, U9.20, U11.20
D15: J1.16, J6.31, U2.58, U9.21, U11.21
DTACK: J3.3, RN1.2, U2.10, U4.10, U12.10
FC0: J3.16, U2.30, U6.9
FC1: J3.18, U2.29, U6.10
FC2: J3.20, U2.28, U6.12
GND: C1.2, C2.2, C4.2, C5.2, C6.2, C7.2, C8.2, C9.2, C10.2, C11.2, C12.2, C13.2, C14.2, C15.2, C16.1, C17.1, J2.2, J3.39, J3.40, J4.6, J5.6, J6.1, J6.8, J6.9, J6.10, J6.11, J6.12, J6.14, J6.15, J6.16, J6.17, J6.39, J6.50, R11.2, R20.2, R21.2, SW1.1, U1.7, U2.16, U2.17, U2.56, U2.57, U3.7, U4.7, U5.7, U6.7, U7.8, U8.16, U9.16, U10.16, U11.16, U12.22
HALT: D1.2, J3.11, R9.2, U2.19, U4.2
IACK: J3.28, JP6.1, U6.8
IORD: J6.34, U1.8
IOSEL: J3.35, U6.4, U7.7, U12.39
IOWR: J6.35, U1.11
IP4: J3.36, U12.43
IP5: J3.38, U12.42
IPL0: J3.22, RN1.9, U2.27
IPL1: J3.24, JP5.2, RN1.8, U2.26
IPL2: J3.26, RN1.7, U2.25
LDS: J3.8, U2.8, U5.2, U5.5
unnamed: C15.1, R12.2, SW1.2, U3.13
unnamed: C16.2, U12.36, Y2.2
unnamed: C17.2, U12.37, Y2.1
unnamed: D1.1, R11.1
unnamed: D2.1, U12.30
unnamed: D2.2, R16.1
unnamed: D3.1, U12.16
unnamed: D3.2, R17.1
unnamed: D4.1, U12.29
unnamed: D4.2, R18.1
unnamed: D5.1, U12.17
unnamed: D5.2, R19.1
unnamed: J4.1, U12.8
unnamed: J4.2, U12.33
unnamed: J4.3, U12.35
unnamed: J4.4, JP3.2
unnamed: J4.5, U12.32
unnamed: J5.1, U12.5
unnamed: J5.2, U12.13
unnamed: J5.3, U12.11
unnamed: J5.4, JP4.2
unnamed: J5.5, U12.14
unnamed: JP2.2, U6.5
unnamed: R6.2, U2.23
unnamed: R13.1, R14.2, U3.4, U3.5
unnamed: R13.2, U3.3, Y1.1
unnamed: R15.2, U4.11, U4.12
unnamed: R20.1, SW3.1, U12.3
unnamed: R21.1, SW2.1, U12.40
unnamed: U3.8, U6.2
unnamed: U3.10, U6.1
unnamed: U3.12, U4.1, U4.3
unnamed: U4.13, U6.6
OP2: J3.32, U12.31
OP3: J3.34, U12.15
RAMSEL: J3.23, U7.14, U10.22, U11.22
RD: J3.12, U1.10, U3.2, U5.1, U5.9
RD-L: U5.3, U8.24, U10.24
RD-U: U5.8, U9.24, U11.24
RESET: J3.13, RN1.5, U2.20, U4.4, U12.38
ROMSEL: J3.19, JP1.2, U8.22, U9.22
R~W: J3.10, J3.14, U1.13, U2.9, U3.1, U5.4, U5.12, U12.9
SIACK: JP6.2, U12.41
SIRQ: JP5.1, U12.24
UDS: J3.6, U2.7, U5.10, U5.13
WR-L: U5.6, U8.31, U10.29
WR-U: U5.11, U9.31, U11.29

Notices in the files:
boards/techy-robot__Mighty-Micro-Motors__stm32g070_and_DRV8311_single_motor_board_-_V1_Alpha/unrouted.kicad_pcb:
© 2024 Asher James Edwards
